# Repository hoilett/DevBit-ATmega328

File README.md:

# DevBit-ATmega328
CalvEngIO DevBit board for the ATmega328. This board is inspired by SparkFun's Arduino Pro Mini. As an upgrade, we broke out all the analog pins for easy access. We also broke out AREF.

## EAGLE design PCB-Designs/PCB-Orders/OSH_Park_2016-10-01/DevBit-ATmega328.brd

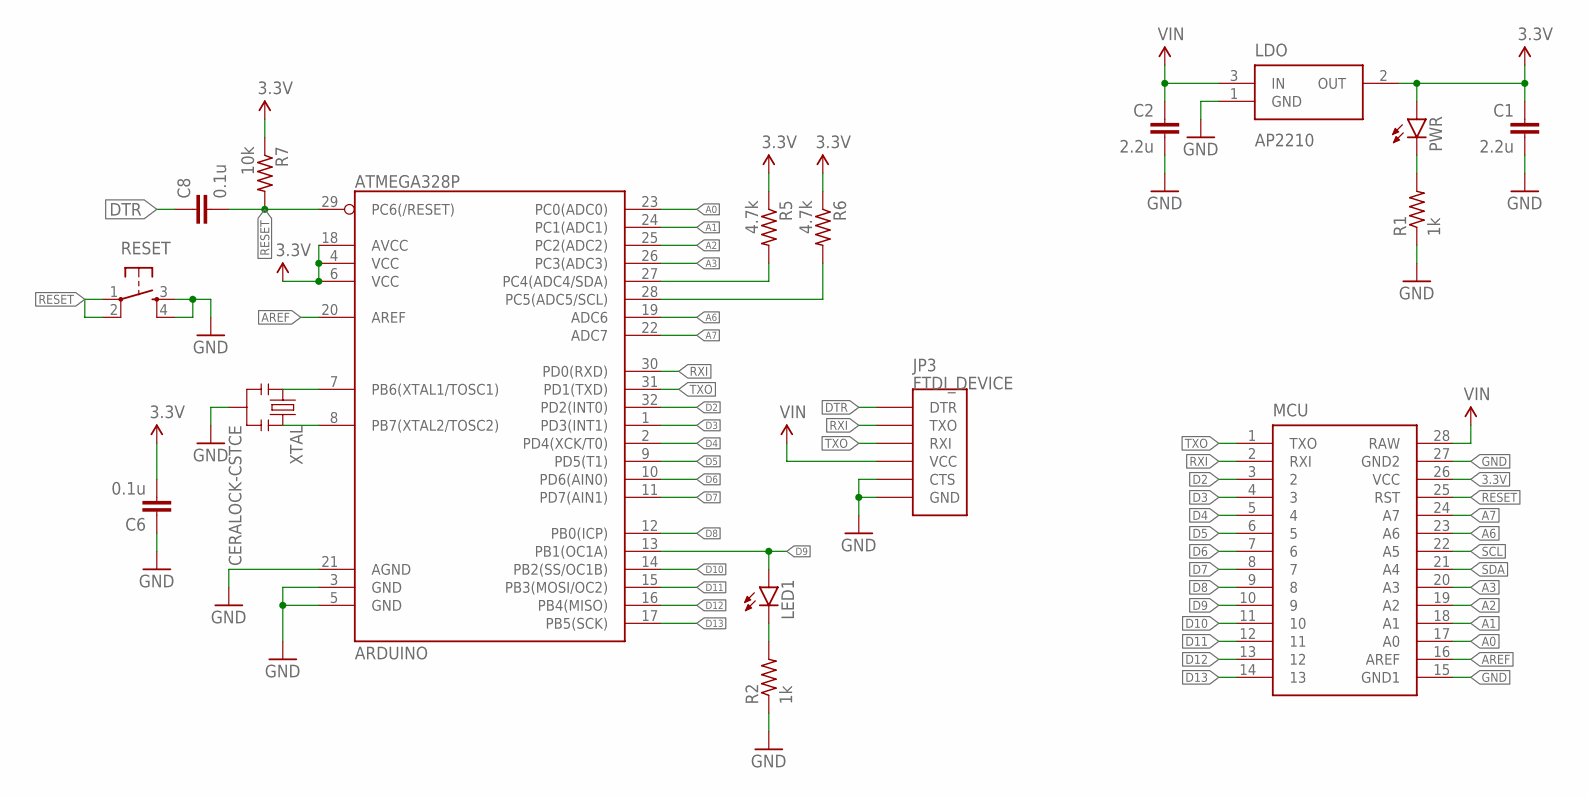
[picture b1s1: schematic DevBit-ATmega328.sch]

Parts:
ARDUINO: ATMEGA328P; TQFP32-08
C1, C2: 2.2u; C0402
C6, C8: 0.1u; C0402
JP3: FTDI_DEVICE
LDO: AP2210; SOT23
LED1: LED0603; LED-0603
MCU: DEVBASIC-V1; DEVBIT-BASIC-V1
PWR: LED0603; LED-0603
R1, R2: 1k; R0402
R5, R6: 4.7k; R0402
R7: 10k; R0402
RESET: BUTTON-PTS830GG140; BUTTON-GULLWING
XTAL: CERALOCK-CSTCE; RESONATOR-00

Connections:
3.3V: ARDUINO.4 (VCC), ARDUINO.6 (VCC), ARDUINO.18 (AVCC), C1.1, C6.2, LDO.2 (OUT), MCU.26 (VCC), PWR.A, R5.1, R6.1, R7.1
A0: ARDUINO.23 (PC0(ADC0)), MCU.17 (A0)
A1: ARDUINO.24 (PC1(ADC1)), MCU.18 (A1)
A2: ARDUINO.25 (PC2(ADC2)), MCU.19 (A2)
A3: ARDUINO.26 (PC3(ADC3)), MCU.20 (A3)
A6: ARDUINO.19 (ADC6), MCU.23 (A6)
A7: ARDUINO.22 (ADC7), MCU.24 (A7)
AREF: ARDUINO.20 (AREF), MCU.16 (AREF)
D2: ARDUINO.32 (PD2(INT0)), MCU.3 (2)
D3: ARDUINO.1 (PD3(INT1)), MCU.4 (3)
D4: ARDUINO.2 (PD4(XCK/T0)), MCU.5 (4)
D5: ARDUINO.9 (PD5(T1)), MCU.6 (5)
D6: ARDUINO.10 (PD6(AIN0)), MCU.7 (6)
D7: ARDUINO.11 (PD7(AIN1)), MCU.8 (7)
D8: ARDUINO.12 (PB0(ICP)), MCU.9 (8)
D9: ARDUINO.13 (PB1(OC1A)), LED1.A, MCU.10 (9)
D10: ARDUINO.14 (PB2(SS/OC1B)), MCU.11 (10)
D11: ARDUINO.15 (PB3(MOSI/OC2)), MCU.12 (11)
D12: ARDUINO.16 (PB4(MISO)), MCU.13 (12)
D13: ARDUINO.17 (PB5(SCK)), MCU.14 (13)
DTR: C8.1, JP3.DTR
GND: ARDUINO.3 (GND), ARDUINO.5 (GND), ARDUINO.21 (AGND), C1.2, C2.2, C6.1, JP3.CTS, JP3.GND, LDO.1 (GND), MCU.15 (GND1), MCU.27 (GND2), R1.1, R2.1, RESET.3, RESET.4, XTAL.2
unnamed: ARDUINO.7 (PB6(XTAL1/TOSC1)), XTAL.1
unnamed: ARDUINO.8 (PB7(XTAL2/TOSC2)), XTAL.3
unnamed: PWR.C, R1.2
unnamed: LED1.C, R2.2
RESET: ARDUINO.29 (PC6(/RESET)), C8.2, MCU.25 (RST), R7.2, RESET.1, RESET.2
RXI: ARDUINO.30 (PD0(RXD)), JP3.TXO, MCU.2 (RXI)
SCL: ARDUINO.28 (PC5(ADC5/SCL)), MCU.22 (A5), R6.2
SDA: ARDUINO.27 (PC4(ADC4/SDA)), MCU.21 (A4), R5.2
TXO: ARDUINO.31 (PD1(TXD)), JP3.RXI, MCU.1 (TXO)
VIN: C2.1, JP3.VCC, LDO.3 (IN), MCU.28 (RAW)

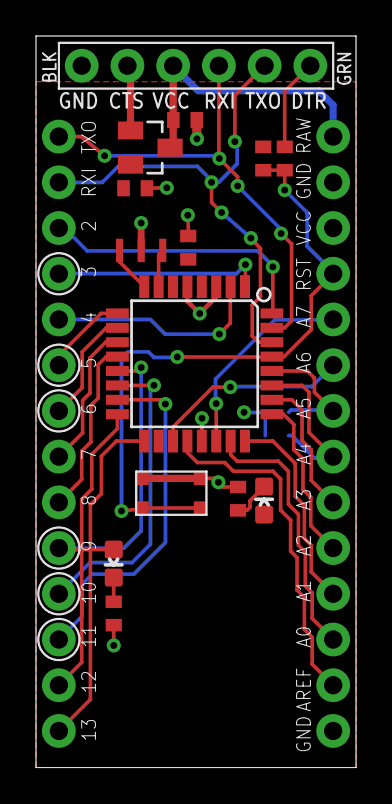
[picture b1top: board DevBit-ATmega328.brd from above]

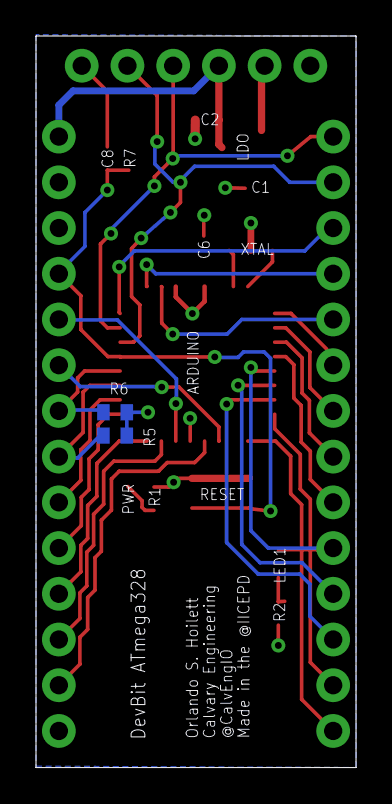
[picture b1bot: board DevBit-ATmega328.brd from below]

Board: 2 copper layers, 17.8 x 40.6 mm, 17 parts (2 on the bottom side), 32 nets.

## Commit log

2016-10-01 Create LICENSE-hardware
2016-10-03 first prototypes

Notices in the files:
PCB-Designs/DevBit-ATmega328.sch:
Creative Commons License
parts and their libraries:
SparkFun-DigitalIC: Licensing: Creative Commons ShareAlike 4.0 International - https://creativecommons.org/licenses/by-sa/4.0
